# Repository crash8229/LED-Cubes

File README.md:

# LED-Cubes
A repo to hold my LED cube related projects.

## Raspberry Pi PICO Setup
Getting Started Guide: https://datasheets.raspberrypi.com/pico/getting-started-with-pico.pdf.

Requires the Pico C++ SDK. Instructions are provided in the Getting Started Guide.

Make sure the `PICO_SDK_PATH` environment variable is set. You may need to set the variable in your IDE as well.

If using the Picoprobe for development.
Refer to the `Appendix A: Using Picoprobe` section of the Getting Started Guide to set things up.

If using the Pi Debug Probe for development.
Refer to this webpage to set things up: https://www.raspberrypi.com/documentation/microcontrollers/debug-probe.html 

I use openocd and have created config files under [`program/rpi_pico_driver/openocd_targets`](program/rpi_pico_driver/openocd_targets) for using the Picoprobe and Pi Debug Probe.
These simply combined the needed config files that came with openocd for ease of use.

### CLion Setup
You will need set the environment variables used by CMake.
This is done by going to `File > Settings... > Build, Exexution, Deployment > CMake`.
With a profile selected, add variables to the Environment field.
The only one currently needed is the `PICO_SDK_PATH` variable that points to the location of the Pico SDK.

There are 2 ways to set up the Run/Debug configurations: `OpenOCD Download & Run` or `Embedded GDB Server`

#### OpenOCD Download & Run
This is the preferred way as it allows one to run or debug the program.

If using the Picoprobe, create an `OpenOCD Download & Run` configuration and configure as shown below: 
If using the Pi Debug Probe, create an `OpenOCD Download & Run` configuration and configure as shown below: 

#### Embedded GDB Server
This way only allows one to debug the program.

If using the Picoprobe, create an `Embedded GDB Server` configuration and configure as shown below: 
If using the Pi Debug Probe, create an `Embedded GDB Server` configuration and configure as shown below: 

### VSCode Setup
WIP (Need to get it working)

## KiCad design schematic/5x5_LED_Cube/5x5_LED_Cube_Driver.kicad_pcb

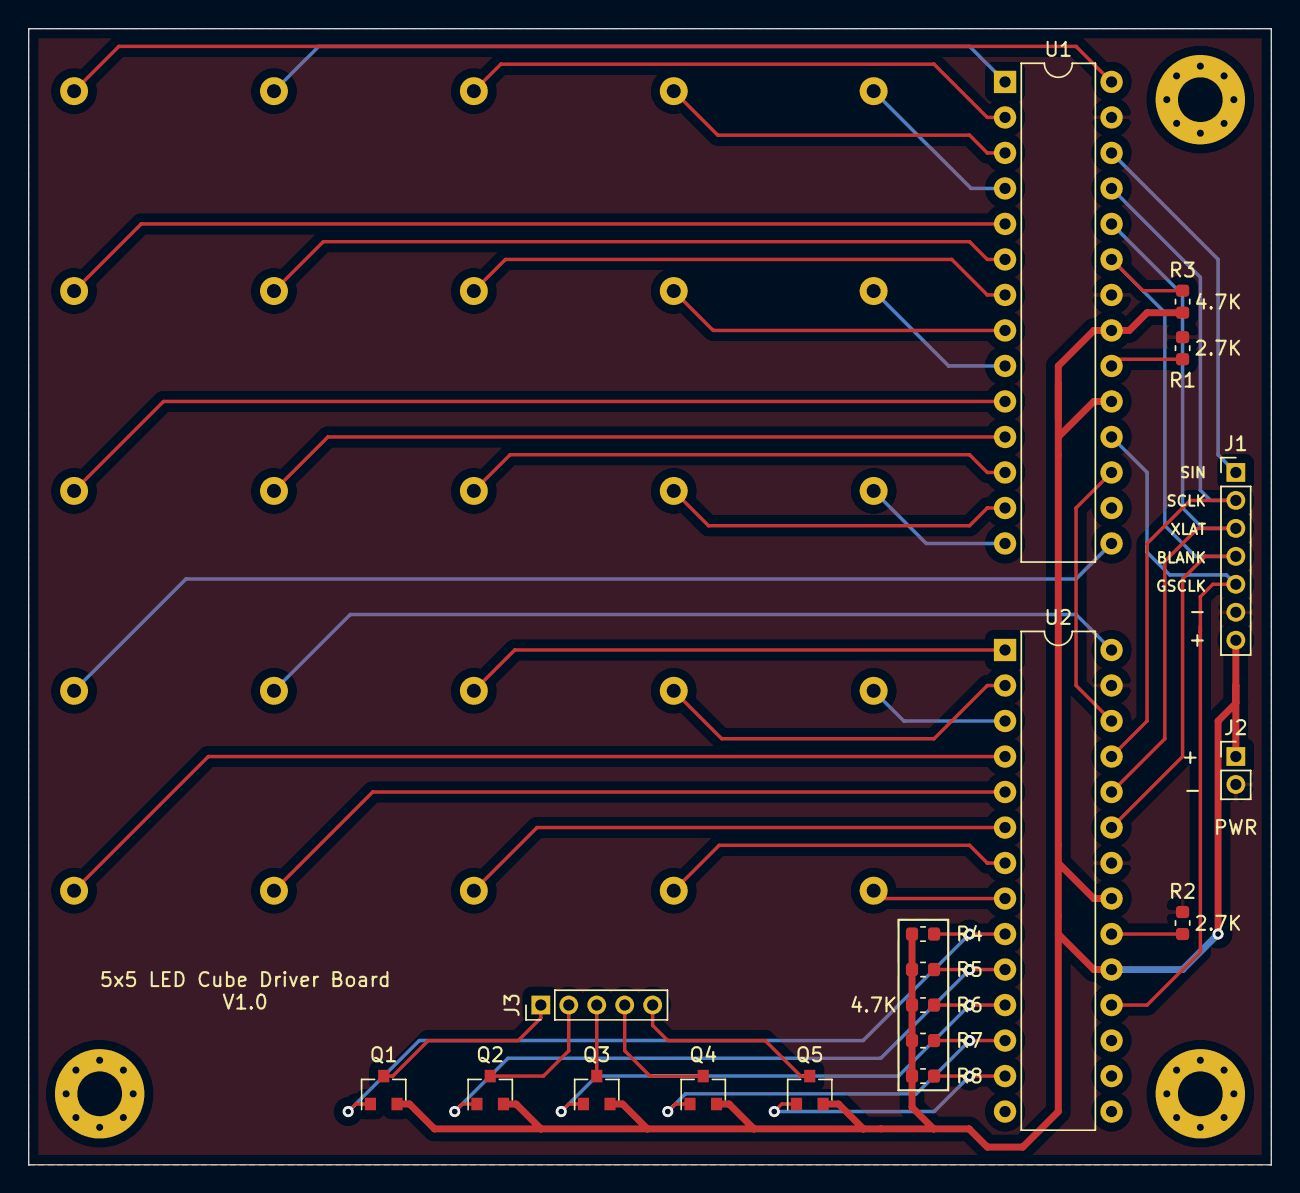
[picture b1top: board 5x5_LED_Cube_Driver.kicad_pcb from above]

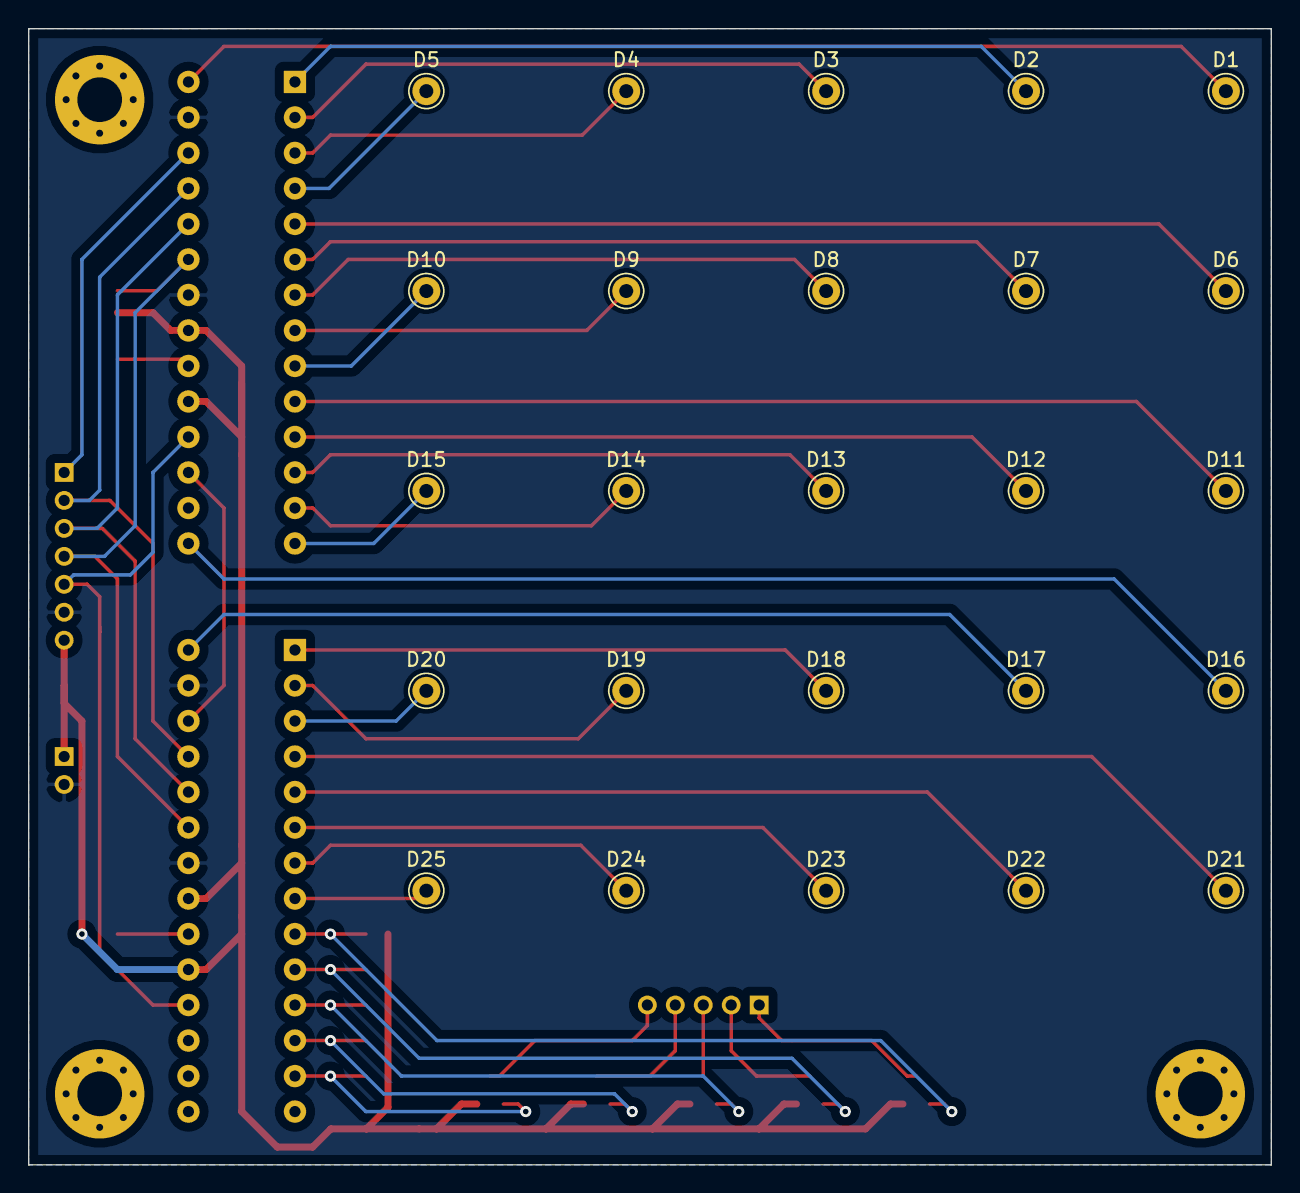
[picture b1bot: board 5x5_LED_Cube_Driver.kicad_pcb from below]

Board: 2 copper layers, 88.9 x 81.3 mm, 43 parts (25 on the bottom side), 45 nets.

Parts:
D1, D2, D3, D4, D5, D6, D7, D8, D9, D10, D11, D12, D13, D14, D15, D16, D17, D18, D19, D20, D21, D22, D23, D24, D25: LED; Pin_D1.0mm_L10.0mm
J1: Arduino; PinHeader_1x07_P2.00mm_Vertical
J2: Power; PinHeader_1x02_P2.00mm_Vertical
J3: Layers; PinHeader_1x05_P2.00mm_Vertical
Q1, Q2, Q3, Q4, Q5: DMG2305UX; SOT-23
R1, R2: 2.7K; R_0603_1608Metric
R3, R4, R5, R6, R7, R8: 4.7K; R_0603_1608Metric
U1, U2: TLC5940NT; DIP-28_W7.62mm

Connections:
+5V: J1.7, J2.1, Q1.2, Q2.2, Q3.2, Q4.2, Q5.2, R3.2, R4.1, R5.1, R6.1, R7.1, R8.1, U1.19, U1.21, U2.19, U2.21
/ArduinoD3(GSCLK): J1.5, U1.18, U2.18
/ArduinoD9(XLAT): J1.3, U1.24, U2.24
/ArduinoD10(BLANK): J1.4, R3.1, U1.23, U2.23
/ArduinoD11(SIN): J1.1, U1.26
/ArduinoD13(SCLK): J1.2, U1.25, U2.25
/IREF1: R1.1, U1.20
/IREF2: R2.1, U2.20
/LED1: D1.1, U1.28
/LED2: D2.1, U1.1
/LED3: D3.1, U1.2
/LED4: D4.1, U1.3
/LED5: D5.1, U1.4
/LED6: D6.1, U1.5
/LED7: D7.1, U1.6
/LED8: D8.1, U1.7
/LED9: D9.1, U1.8
/LED10: D10.1, U1.9
/LED11: D11.1, U1.10
/LED12: D12.1, U1.11
/LED13: D13.1, U1.12
/LED14: D14.1, U1.13
/LED15: D15.1, U1.14
/LED16: D16.1, U1.15
/LED17: D17.1, U2.28
/LED18: D18.1, U2.1
/LED19: D19.1, U2.2
/LED20: D20.1, U2.3
/LED21: D21.1, U2.4
/LED22: D22.1, U2.5
/LED23: D23.1, U2.6
/LED24: D24.1, U2.7
/LED25: D25.1, U2.8
/Layer1: J3.1, Q1.3
/Layer1Gate: Q1.1, R4.2, U2.9
/Layer2: J3.2, Q2.3
/Layer2Gate: Q2.1, R5.2, U2.10
/Layer3: J3.3, Q3.3
/Layer3Gate: Q3.1, R6.2, U2.11
/Layer4: J3.4, Q4.3
/Layer4Gate: Q4.1, R7.2, U2.12
/Layer5: J3.5, Q5.3
/Layer5Gate: Q5.1, R8.2, U2.13
/SOUT1: U1.17, U2.26
GND: J1.6, J2.2, R1.2, R2.2, U1.22, U1.27, U2.22, U2.27

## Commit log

2019-11-03 Added TLC5940 resistance calculation for IREF
2019-11-04 Completed schematic for the 5x5 LED Cube
2019-11-04 Started on pcb for 5x5 LED Cube
2019-11-06 Added custom library to hold custom componets and removed unused .pro file
2019-11-07 Added headers for layers and arduino input
2019-11-07 Updated PCB to latest schematic changes
2019-11-08 Routed more PCB traces and added power header
2019-11-11 Created jigs to help with assembly
2019-11-11 Added retaining ring to full jig
2019-11-11 Finished PCB routing
2019-11-12 Removed traces and rearannged footprints a little
2019-11-13 Added traces for Arduino side
2019-11-14 Fixed the jigs again and add a spacer
2019-11-15 PCB shrunken to the max
2019-11-15 Finished PCB
2019-11-15 5x5 LED Cube: Renamed project files
2019-11-15 Removed cache
2019-11-17 Simple test program for the 5x5 LED cube
2019-11-17 Replaced the SIP resistor with SMD ones
2019-11-18 Grouped the PCB traces for layers closer together
2019-11-23 Fixed the headers being too small for the wires
2021-02-20 Push gdrive files to consolidate them
2021-11-02 Reorganized files
2021-11-02 Pushed RPi code to control TLC5940
2021-11-17 Removed dot correction
2021-11-24 Improved grayscale methods Reduced CPU usage and time
2021-11-24 Renamed folder Added new class and waveform workspace
2021-12-11 Added 5x5 LED cube RPi Pico driver
2021-12-11 Renamed pico driver folder
2021-12-11 Removed Arduino code
2021-12-11 Renamed zero driver folder
2021-12-11 Renamed files
2021-12-18 Use environment variable for finding SDK
2022-03-20 Added more functions to w25q64 driver
2022-03-21 Add submodule for SD FatFs driver
2022-03-23 TLC5940: Added another constructor and removed pointer and const type from cfg
2022-03-23 SD card configured correctly
2022-03-23 Removed W25Q64 drivers Created gist to save it: https://gist.github.com/crash8229/80564c2459fed3c32448bc0d704f42ea
2022-03-26 Moved submodule location
2022-03-27 Reorganized file structure of project
2022-03-27 Added RPi Pico setup to README.md
2022-03-27 Added .idea folder for LED-Cubes
2022-03-27 Moved kicad files to its own folder.
2022-03-27 Moved rpi_zero_driver up a folder
2022-03-27 Moved WaveForm & hterm files
2022-03-27 Moved rpi_pico_driver up a folder
2022-03-28 Moved config.h up a folder
2022-03-28 tlc5940: Created default constructor and public init functions
2022-03-28 Created SD_DRIVE constant in config.h to hold logical drive number
2022-03-29 Created LEDCube class Got SD card binary read working
2022-03-29 Renamed variables to follow CamelCasing
2022-03-29 Commented out DEBUG define
2022-03-29 Forked spi_sd_fat submodule to modify some debug print code
2022-03-29 Disabled LED usage for sd card library
2022-03-29 Cleaned up code
2022-03-29 Added loading bar pattern
2022-04-02 Added useful documents Moved TLC5940_IREF.xlsx to doc
2022-04-02 Restructured repo again
2022-05-02 Added wait in main to allow debugger to set breakpoints
2022-05-02 Added intial version of the file specification
2022-05-03 Fixed formatting of spreadsheet
2022-05-03 Reordered the data type IDs
2022-05-05 Definition files of the v1 file specification
2022-05-05 Updated ksy imports
2022-05-07 Renamed file.ksy to allow the visualizer to work
2022-05-07 Finished cube_file.ksy
2022-05-07 Created master parser
2022-05-21 Initial push of the ledcube Python module
2022-05-22 Abstracted ksy processing Fixed mypy errors
2022-05-22 Fixed incorrect assembly of the builder string
2022-05-22 Added frame and animation builders
2022-05-23 Added library and cube_file builders Moved code into a Builder class
2022-05-23 Renamed builder to serializer
2022-05-23 Added test case for cube_file
2022-05-23 Moved code to make out dir into Serializer
2022-05-23 Removed unused imports
2022-05-27 Separated classes
2022-05-27 Made build serializers script executable
2022-05-27 Removed unneeded pytest import
2022-05-27 Added script to patch parser.py
2022-05-27 Added stubs and config for mypy
2022-05-27 Removed unsued dictionary entries
2022-05-27 Added test cases for parsers
2022-05-28 Moved animation CRC to the end of the definition
2022-05-29 Moved CRC in library v1 after the secondary header
2022-06-18 Write out imports/custom types to out module Reference these when building the final struct
2022-06-19 Generated valid CRC for test files
2022-06-20 Added assemblers for frame v1 and animation v1
2022-06-20 Updated test files Fixed animation data length Added valid CRC
2022-06-20 Finished assemblers for V1
2022-06-20 Removed ubnsued Template class Added error handling for __len__
2022-11-05 Updated license information in toml file
2022-11-07 Moved Python module to its own repository https://github.com/crash8229/led-cube-data
2023-05-10 Updated README.md to include Pi Debug Probe set up and better CLion Run/Debug configuration set up.
2023-05-10 Updated spi_sd_fat submodule to pull in the latest updates upstream Abstracted the SD card code into its own class The SD card code in main.cpp now runs on the second core Increased the SD card clock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
2023-05-11 Replaced 24 with the constant variable GRAYSCALE_BIT_SIZE in tlc5940 Removed the static keyword from the unmount method definition in the sdcard class
2023-05-11 Moved SD card read rate test code to its own method
2023-05-11 Started updating the schematic to include the pico and sd card module
2023-05-11 Added pico symbol to schematic
2023-05-14 Updated schematic to include the RPi Pico and SD card module
2023-05-14 Updated SD card read test and configured the speed to the fastest stable rate
2023-05-14 Initial pass at updating to use SDIO for the SD card
2023-05-14 Hack to get it to build Related Git issue: https://github.com/raspberrypi/pico-sdk/issues/1368
2023-05-14 Workaround to issue: https://github.com/raspberrypi/pico-sdk/issues/1368
    Seems that setting `PICO_CXX_ENABLE_EXCEPTIONS` to 1 prevents `-nostartfiles` from being set. `-nostartfiles` seems to cause the build issues.
2023-05-15 Implemented SDCard::isFileOpen
2023-05-15 Finished configuring SD card for use with SDIO Had to rearrange both the SD card module and TLC pin layouts Removed unneeded pins to drive the TLCs
2023-05-15 Allowed the SD card test to be toggled via a define statement Also added an option for the SD test to run indefinitely
2023-05-17 Updated schematic to wire up the SD card module to the pico
2023-05-19 Moved the SD card pinout table and instructions on selecting pins to config.h.
2023-05-19 Deinit gpio pins upon destruction of TLC5940 instance
2023-05-19 Updated schematic and footprints
2023-05-20 Fixed bug in SD card read test that would make results invalid after a period of time of running
2023-05-20 Pattern to turn on all the LEDs in the cube
2023-05-20 Updated config.h to use constant type variables to set global parameters Updated files as needed to use the global constants
2023-05-20 Made UART TX/RX configurable
    Init UART and USB stdio directly
2023-05-20 Made pattern for 3x3 cube in the 5x5 cube
2023-05-21 Added ledAllOn method to the TLC5940 class
2023-05-21 Code cleanup
2023-05-21 Formatting and comments
2023-05-22 sdcard.h/.cpp: Create the SD card configuration inside the SD card class and prevent trying to use the same drive in different instances Added function to get the card configuration Added function to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
    config.h:
    Made the STDIO UART and USB toggleable
    Added definition for PIO SDIO configuration
    Added defines for FatFS configuration to ensure the settings I want are set
2023-05-22 Updated schematic to use the Pico for power
2023-05-26 Added connections for the rotary encoder and pin socker for the oled display
2023-05-26 sdcard.h/.cpp Added SPI support Drive numbers are now handled automatically by the class Added file size function The open file function handles attaching the drive number to the file path
    main.cpp
    Updated SD card read test to avoid getting cached reads and get the true read rate
2023-05-26 Added submodule for Kaitai Struct runtime
2023-05-26 Added submodule for my led-cube-data repository
2023-05-29 Updated kaitai struct submodule to point to my fork
2023-05-29 Added parsers for the led cube file spec
2023-05-29 Updated schematic for 5x5 cube to use new symbol/footprint for oled display
2023-05-29 Added custom libraries to KiCad project
2023-05-29 Added submodule for Pico KiCad symbol and footprint
2023-05-29 Added submodule for My Library
2023-05-29 Updated library paths to point to submodules for portability
2023-05-29 Update submodule
2023-05-30 Updated kaitai struct submodule
2023-05-30 Removed namespace from parsers Added sandbox folder to .gitignore
2023-05-31 Removed kaitai struct parsers
2023-05-31 Removed kaitai struct and led-cube-data submodules
2023-06-02 Added first light parsers ParserBase & PrimaryHeader class
2023-06-04 Added Frame parser
2023-06-06 Added Animation parser Moved the parser test prints to their own class
2023-06-07 Added Library parser
2023-06-07 Added File parser
    Moved parser test to its own function
2023-06-07 Moved test files to the /test folder on the SD card
2023-06-08 Fixed bug when trying to extract the sha256 and name Moved hexStr function to ParserBase
2023-06-08 Renamed hexStr to getHexString and refactored parameters to match definitions in ParserBase
2023-06-10 Moved hardware related .cpp files to their own folder
2023-06-10 Swapped card and tlc code in main.cpp Fixed formatting in test.cpp
2023-06-11 Modified the getPayload functions to return by value the payload instead of using pointers
2023-06-11 Created version of the getPayload function that have no arguments for the frame, animation, and file classes
2023-06-11 Use the instance method to unmount the SD card in the destructor
2023-06-12 Modified parsers classes to use fixed size uints
2023-06-15 Store the name and sha256 as char arrays
2023-06-19 Initial code of the LED cube driver
2023-06-28 Added closeAnimation and isAnimationOpen to led cube driver
2023-06-28 Edited comments in config.h
